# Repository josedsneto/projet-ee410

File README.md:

# Détecteur de chute

Nous souhaitons développer un capteur de chute, à l'aide d'un axéléromètre 3 Axes.
Lorsqu'une chute est détectée : 
- Une alerte via un vibreur est transmise à l'utilisateur.
- Il dispose de 10 secondes pour confirmer qu'il ne s'est pas évanoui via un bouton.
- Si il a confirmé qu'il était conscient, rien ne se passe.
- En revanche, si il n'a rien confirmé alors une alerte est envoyé par bluetooth sur le téléphone.

## Planning et Deadlines

- 04 Octobre 2024 : Choix du système visé (Remettre une page décrivant le système
imaginé, les mesures qui seront faites + toute autre info pertinente) \
Le [lien](https://docs.google.com/document/d/1k7mpjtoi8ii_IY9sKmL_kZ1YLawBmLwHGLVDXy7D6bw/edit?usp=sharing) vers le document
- 17 Octobre 2024 : Commande de composants 
- 24 Octobre 2024 : Evaluation intermédiaire
- 29 Novembre 2024 : Présentation orale
- 06 Décembre 2023 : Rendu du rapport final écrit 

## Critères pour les profs

L'idée est de faire une première application avec un module compatible Arduino. 
Puis de faire une autre version où on part du composant seul (ou package) et de faire un PCB autour du composant.

A la fin, il faudra comparer les deux.\
Dans notre cas, il s'agit d'un tout ou rien : détection ou non détection. \
Mais nous pouvons récupérer les valeurs des accélérations des 2 capteurs et comparer leurs valeurs.\
De plus nous pouvons réaliser un test statistique sur la détection de chute. (exemple en dessous)

| Cas réel -> | Statique | Chute | Marche |
|-------------|:--------:|:-----:|:------:|
| Statique    |   99%    |  1%   |   0%   |
| Chute       |   1.5%   |  98%  |  0.5%  |
| Marche      |    5%    |  25%  |  70%   |

Et aussi pour la comparaison des 2 capteurs

|                | Capteur1 | Capteur2 |
|----------------|:--------:|:--------:|
| Statique       |   99%    |   99%    |
| Marche         |   97%    |   98%    |
| Chute droite   |   80%    |   98%    |
| Chute en avant |   95%    |   95%    |

Et ainsi comparer nos 2 capteurs.\
Certes nous n'avons que des valeurs tout ou rien mais nous pouvons dire par plusieurs paramètres si un capteur est mieux qu'un autre.

### Réalisation de tests

Il va falloir pouvoir réaliser des tests qui sont reproductibles !\
Il faut pouvoir obtenir le même résultat en faisant une même manip plusieurs fois.

- Test de la chute droite : 
    - Récupération des valeurs lorsqu'un humain chute, pour avoir une idée de modèle.
    - On peut modéliser cette chute avec un ballon qui tombe sur un matelas en mousse par exemple. Ceci permettra une certaine reproductibilité.
- Test de la chute en avant : 
    - Pareil, récupération des valeurs pour un humain
    - Modélisation par exemple par un balai qui tombe en avant.

**Notes sur les chutes :**
- Faire attention à l'orientation du capteur, son positionnement sur le témoin
- Pouvoir reproduire la chute en toutes conditions

# Capteur de chute V1

On utilise le code ```CapteurChuteV1.ino```

Lorsqu'une chute se passe voici ce que nous pouvons mesurer : 

Lorsque le module passe en dessous du seuil bas, c'est le début de la chute : la gravité est compensée par la chute.\
Puis on repasse au dessus du seuil haut, c'est lorsqu'on heurte le sol : gravité + impact avec le sol.

Badé sur ce modèle, nous créons le code arduino ```CapteurChuteV1.ino```, qui utilise un diagramme d'état. \
Voici son schéma : 

# Le nouveau capteur

Nous rédigeons un tableau comparatif entre les 2 capteurs : 

|                      |      ADXL 345       |      ADXL 359      |
|----------------------|:-------------------:|:------------------:|
| Interface            |      SPI, I²C       |      SPI, I²C      |
| Technologie utilisée |        MEMS         |        MEMS        |
| Plage de mesure      | ±2g, ±4g, ±8g, ±16g |  ±10g, ±20g, ±40g  |
| Résolution           |       13 bits       |      20 bits       |
| Bruit                |     380 µg/√Hz      |     80 µg/√Hz      |
| 0g Offset            |        ±150 mg      |       ±125 mg      |
| Taille du boîtier    | 3 mm × 5 mm × 1 mm  | 4 mm × 4 mm × 1 mm |

**La technologie MEMS (Micro-Electro-Mechanical Systems).**\
 Un dispositif MEMS est composé de minuscules éléments comme des ressorts, des leviers et des masses mobiles  qui sont gravés sur du silicium.\
 Lorsqu'une force externe (comme une accélération) agit sur ces éléments, cela provoque un mouvement des masses et viens déformer les ressorts. Ce mouvement viens changer la valeur de capacité, ce qui vient influer sur le signal électrique, nous récupérons ainsi des informations sur l'accélération.

Voici le schéma de l'ADXL 359.

| Pin N° | Mnemonic |                                                                                            Description                                                                                            |
|--------|:--------:|:-------------------------------------------------------------------------------------------------------------------------------------------------------------------------------------------------:|
| 1      |   SCL    |                                                                             Serial Communications Clock for I2C (SCL)                                                                             |
| 2      |  Vssio   |                                                                           Connected to Pin 6 (VSSIO) to enable I2C mode                                                                           |
| 3      |   SDA    |                                                                                    Serial Data for I2C (SDA).                                                                                     |
| 4      |   ASEL   |                                                                           Alternate I2C Address Select for I2C (ASEL).                                                                            |
| 5      |  Vddio   |                                                                                 Digital Interface Supply Voltage                                                                                  |
| 6      |  Vssio   |                                                                                          Digital Ground                                                                                           |
| 7      | RESERVED |                                                                    Reserved. This pin can be connected to ground or left open.                                                                    |
| 8      | V1P8DIG  |                                 Digital Supply. This pin requires a decoupling capacitor. If VSUPPLY connects to VSS, supply the voltage to this pin externally.                                  |
| 9      |   Vss    |                                                                                           Analog Ground                                                                                           |
| 10     | V1P8ANA  |                                  Analog Supply. This pin requires a decoupling capacitor. If VSUPPLY connects to VSS, supply the voltage to this pin externally.                                  |
| 11     | VSUPPLY  | Supply Voltage. When VSUPPLY equals 2.25 V to 3.6 V, VSUPPLY enables the internal LDO regulators to generate V1P8DIG and V1P8ANA. For VSUPPLY = VSS, V1P8DIG and V1P8ANA are externally supplied. |
| 12     |   INT1   |                                                                                          Interrupt Pin 1                                                                                          |
| 13     |   INT2   |                                                                                          Interrupt Pin 2                                                                                          |
| 14     |   DRDY   |                                                                                          Data Ready Pin.                                                                                          |

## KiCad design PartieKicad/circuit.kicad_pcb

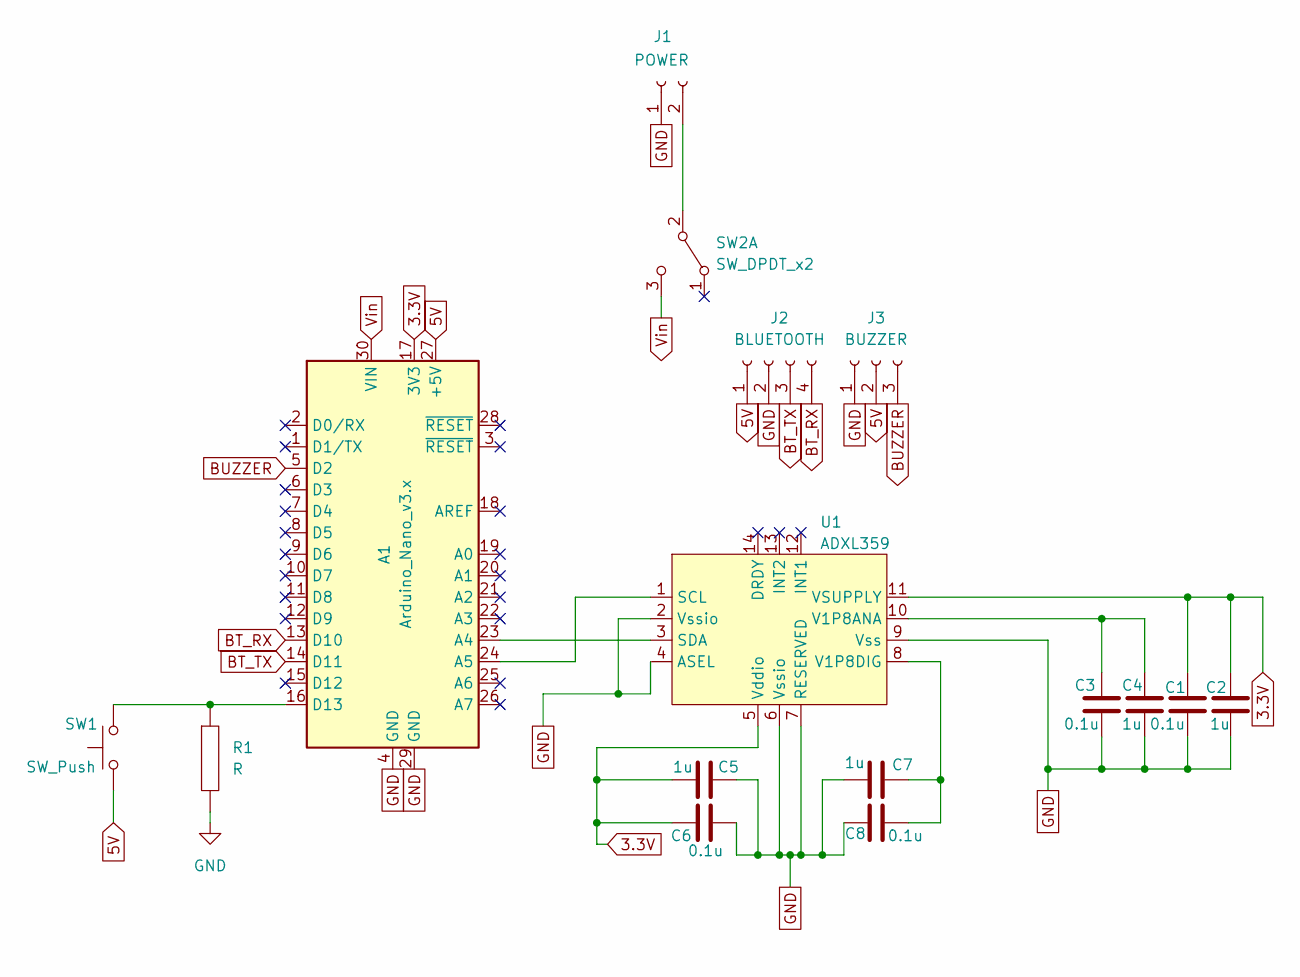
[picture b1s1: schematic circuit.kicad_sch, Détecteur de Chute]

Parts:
A1: Arduino_Nano_v3.x; Arduino_Nano
C1, C3, C6, C8: 0.1u; C_1206_3216Metric
C2, C4, C5, C7: 1u; C_1206_3216Metric
J1: POWER; PinHeader_1x02_P2.54mm_Vertical
J2: BLUETOOTH; PinHeader_1x04_P2.54mm_Vertical
J3: BUZZER; PinHeader_1x03_P2.54mm_Vertical
R1: R; R_1206_3216Metric_Pad1.30x1.75mm_HandSolder
SW1: SW_Push; sw_push_5mm
SW2: SW_DPDT_x2; PinHeader_1x03_P2.54mm_Vertical
U1: ADXL359

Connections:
3.3V: A1.17 (3V3), C1.1, C2.1, C5.2, C6.2, U1.5 (Vddio), U1.11 (VSUPPLY)
5V: A1.27 (+5V), J2.1, J3.2, SW1.1
BT_RX: A1.13 (D10), J2.4
BT_TX: A1.14 (D11), J2.3
BUZZER: A1.5 (D2), J3.3
GND: A1.4 (GND), A1.29 (GND), C1.2, C2.2, C3.2, C4.2, C5.1, C6.1, C7.2, C8.2, J1.1, J2.2, J3.1, R1.2, U1.2 (Vssio), U1.4 (ASEL), U1.6 (Vssio), U1.7 (RESERVED), U1.9 (Vss)
unnamed: A1.23 (A4), U1.3 (SDA)
unnamed: A1.24 (A5), U1.1 (SCL)
unnamed: A1.16 (D13), R1.1, SW1.2
unnamed: J1.2, SW2.2 (B)
unnamed: C3.1, C4.1, U1.10 (V1P8ANA)
unnamed: C7.1, C8.1, U1.8 (V1P8DIG)
Vin: A1.30 (VIN), SW2.3 (C)

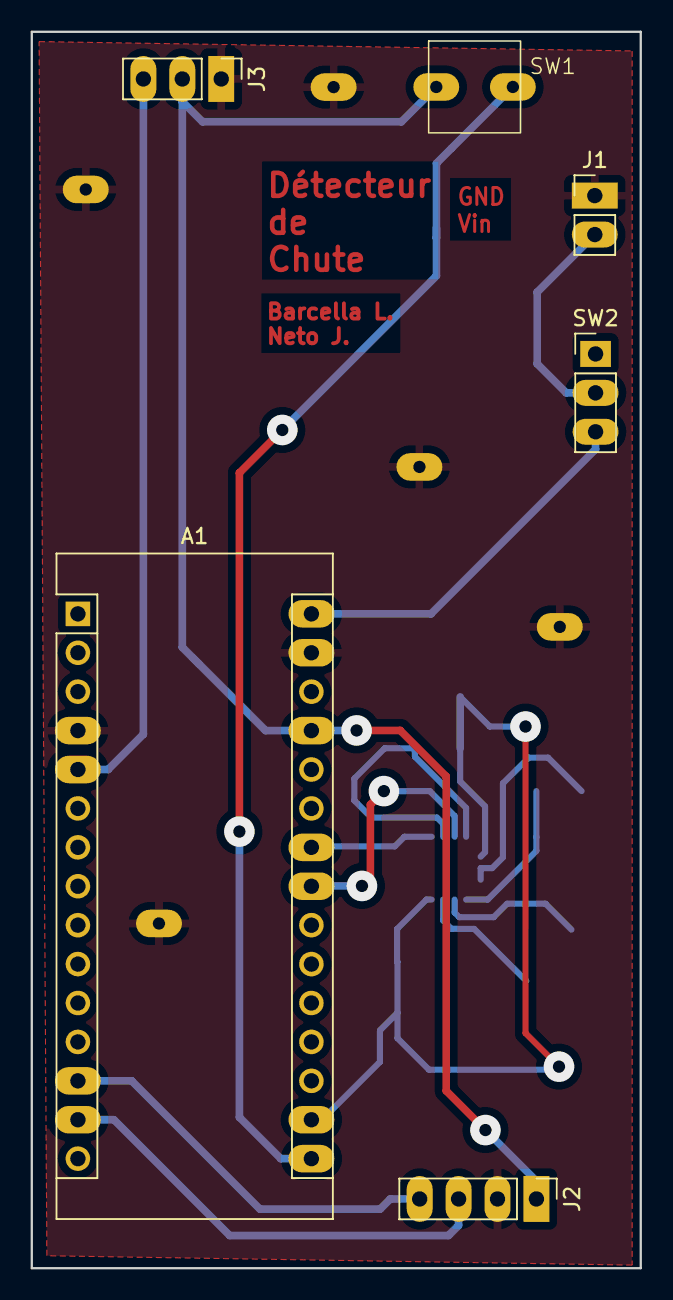
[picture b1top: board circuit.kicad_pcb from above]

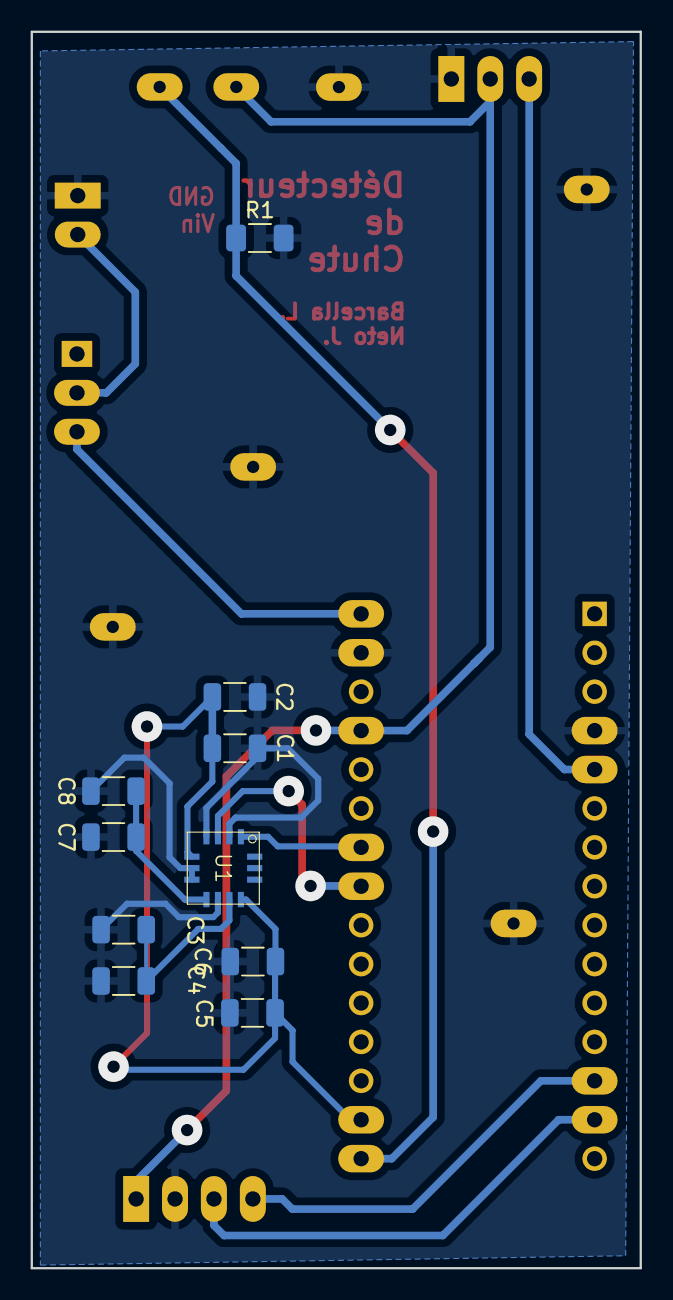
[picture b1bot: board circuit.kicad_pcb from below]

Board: 2 copper layers, 39.7 x 80.7 mm, 16 parts (10 on the bottom side), 13 nets.

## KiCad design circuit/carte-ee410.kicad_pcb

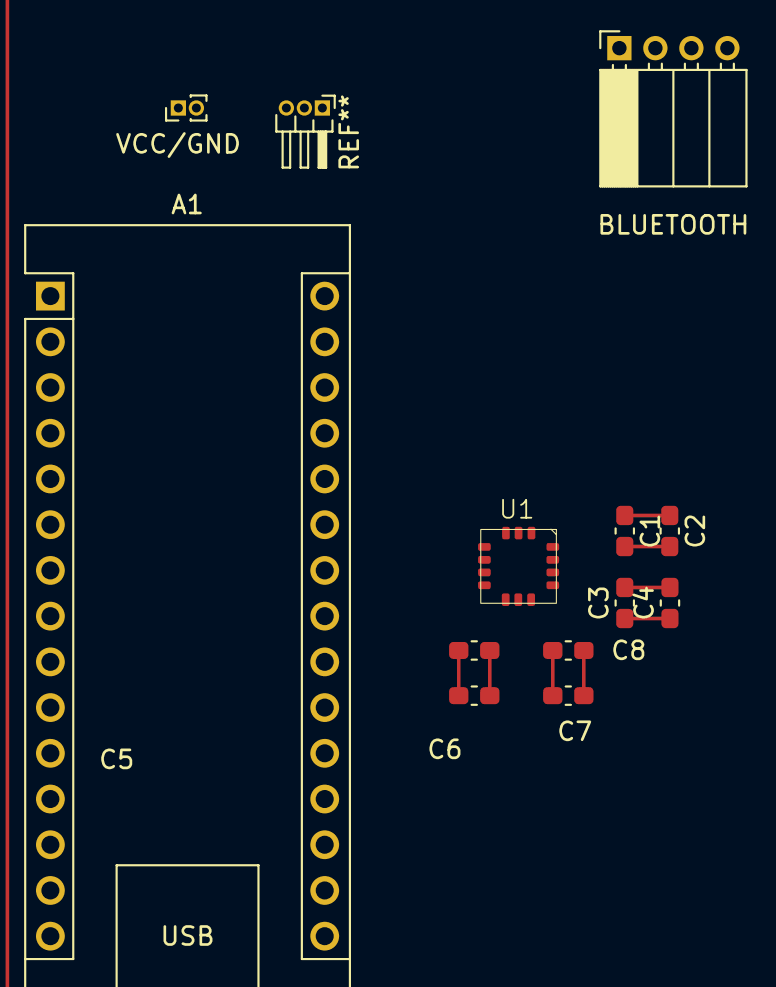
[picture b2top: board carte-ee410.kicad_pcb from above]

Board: 2 copper layers, 12 parts (0 on the bottom side), 9 nets.

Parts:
A1: Arduino_Nano_v2.x; Arduino_Nano
BLUETOOTH: PinSocket_1x04_P2.00mm_Horizontal
C1, C2, C3, C4, C5, C6, C7, C8: C; C_0603_1608Metric_Pad1.08x0.95mm_HandSolder
U1: ADXL363; adxl359
VCC/GND: PinHeader_1x02_P1.00mm_Vertical

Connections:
unnamed: C1.1, C2.1
unnamed: C1.2, C2.2
unnamed: C3.1, C4.1
unnamed: C3.2, C4.2
unnamed: C5.1, C6.1
unnamed: C5.2, C6.2
unnamed: C7.1, C8.1
unnamed: C7.2, C8.2
unnamed: U1.12 (GND), U1.13 (GND)

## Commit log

2024-09-20 Example temperature sensor
2024-09-20 Add Libraries
2024-09-27 add acceleration test
2024-09-27 Add Readme + remove useless file
2024-09-27 Add journal scéance
2024-10-04 add analysis notebook and files to sensor schema
2024-10-04 mine
2024-10-11 add code to capture the acceleration using library example
2024-10-11 Envoie code chute test
2024-10-11 organize libraries
2024-10-11 add capture with module
2024-10-14 Fall Detector Working (V1)
    Détection de chute qui marche quoi !
    En 3h j'ai fait l'éuivalent de 9h de projet...
2024-10-14 Ajustement des valeurs fall detector + images
2024-10-14 Update README (Important à lire !!!!!)
2024-10-24 code python working
2024-10-24 Doc ADXL 359
2024-10-24 Rajout V2 pour traitement données
2024-10-24 Avec le button JOSE
2024-10-24 montage base
2024-10-24 seance demo
2024-11-15 travail séance + début bluetooth
2024-11-16 codes for bluetooth connection
2024-11-17 pcb v1.1
2024-11-19 pcb v2.1
2024-11-20 Travail dernière séance
2024-11-20 Work PCB
    Small Fix on PCB
    + Solve error on the resistance for the button (pcb)
2024-11-22 Ptite Modif
2024-11-22 Data Treatment
2024-11-22 Start Creation Library
    Je débugue la librairie déja donnée pour l'adxl345. Je décode et essaie de tout comprendre...
    Objectif : pouvoir le faire à la main pour plus tard
2024-11-25 code v3
2024-11-25 code with label
2024-11-25 Work on adxl359
    The captor sends data. but we don't know what is happening...
2024-11-27 MatlabCodes (zipped folder)
2024-11-28 Capteur marche
2024-11-28 final code
2024-11-29 Fin du projet
2024-12-06 Cleaning + CR
